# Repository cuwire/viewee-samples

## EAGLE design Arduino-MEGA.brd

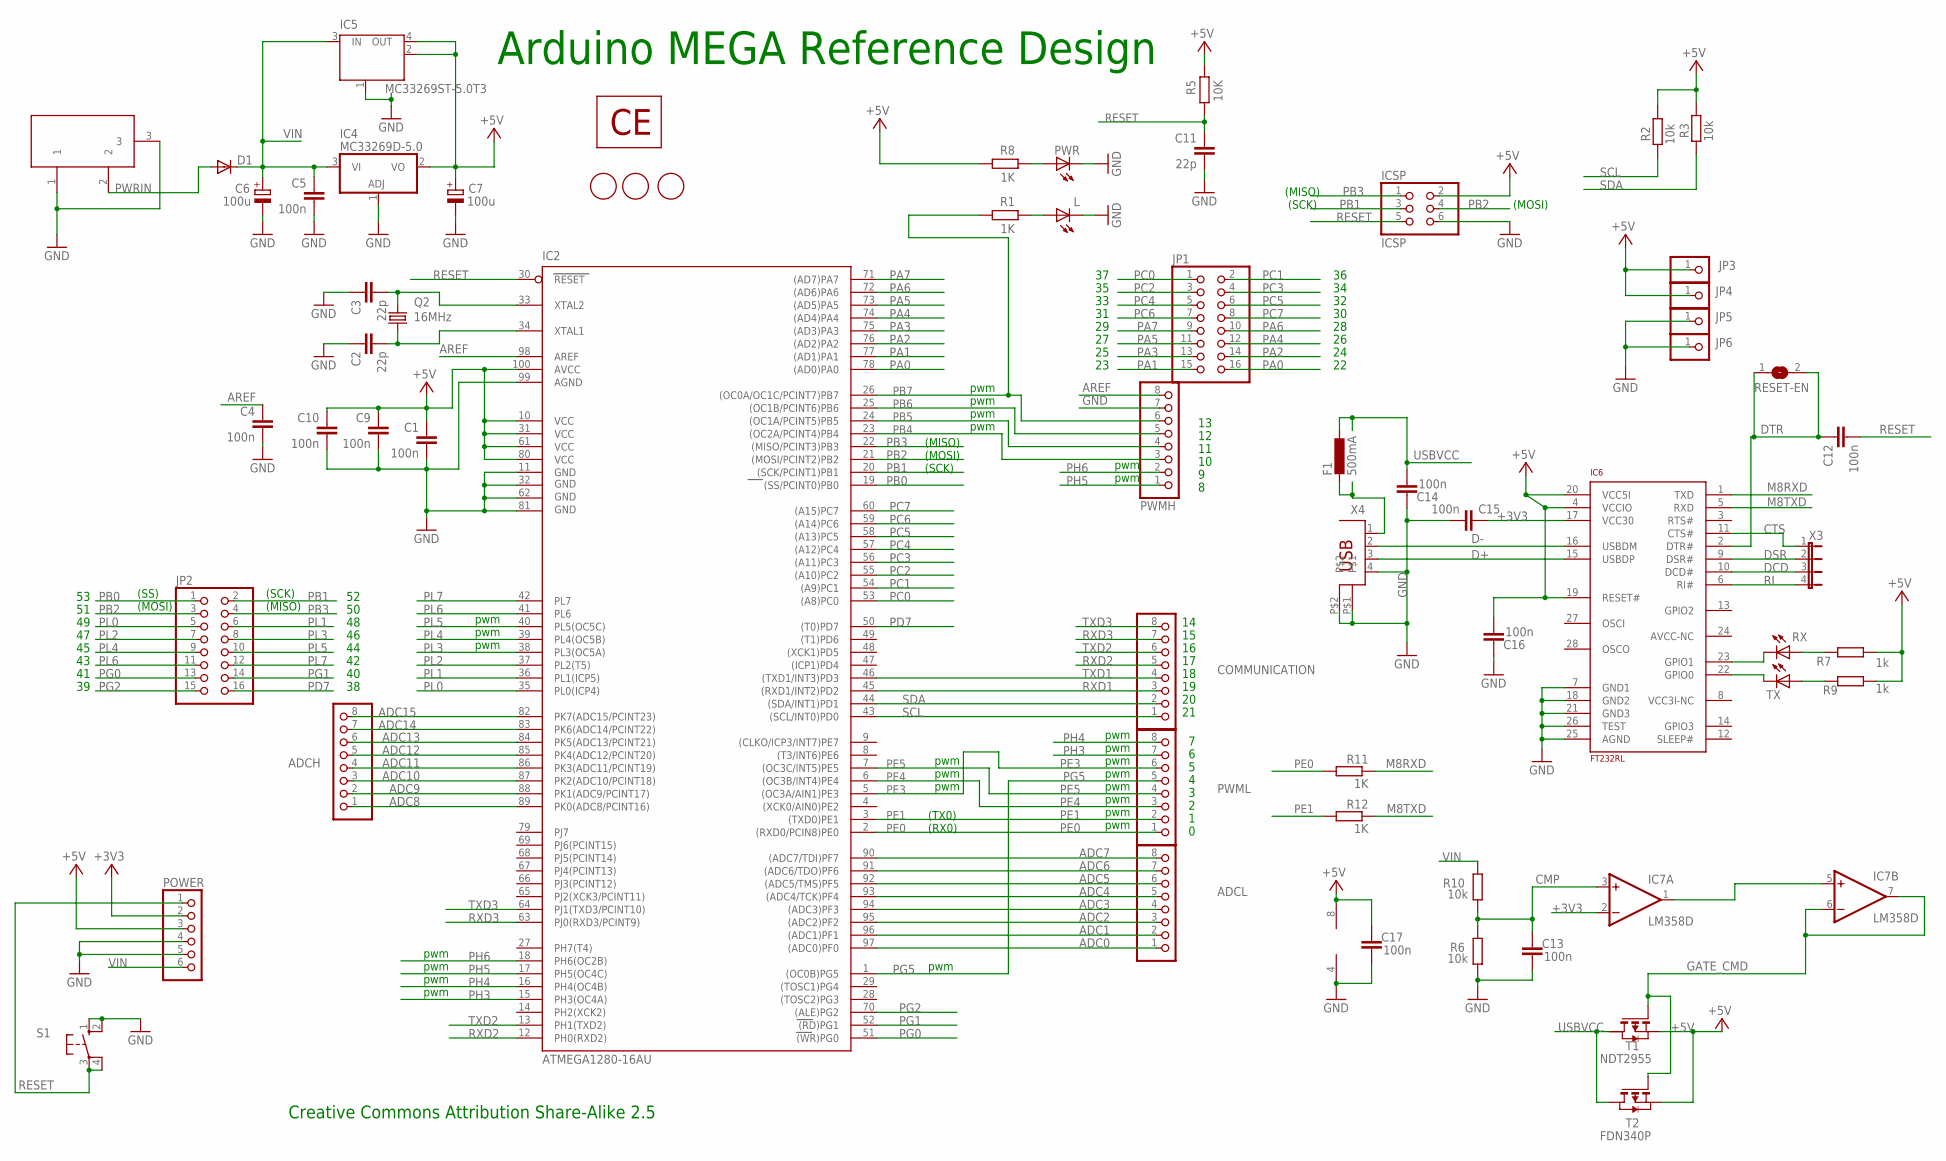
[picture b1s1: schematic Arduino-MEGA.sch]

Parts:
ADCH: PINHD-1X8; 1X08
ADCL: PINHD-1X8; 1X08
C1, C4, C5, C9, C10, C12, C13, C14, C15, C16, C17: 100n; C0805RND
C2, C3, C11: 22p; C0805RND
C6, C7: 100u; SMC_D
COMMUNICATION: PINHD-1X8; 1X08
D1: DIODE-SMB; SMB
F1: 500mA; L1812
IC2: ATMEGA1280-16AU; TQFP100
IC4: MC33269D-5.0; DPACK
IC5: MC33269ST-5.0T3; SOT223
IC6: FT232RL; SSOP28
IC7: LM358D; SO08
ICSP: ICSP; 2X03
JP1, JP2: PINHD-2X8; 2X08
JP3, JP4, JP5, JP6: PINHD-1X1; 1X01
L: LED0805ROUND; 0805RND
POWER: PINHD-1X6; 1X06
PWMH: PINHD-1X8; 1X08
PWML: PINHD-1X8; 1X08
PWR: LED0805ROUND; 0805RND
Q2: 16MHz; HC49/S
R1, R8: 1K; R0805RND
R2, R3, R6, R10: 10k; R0805RND
R5: 10K; R0805RND
R7, R9: 1k; R0805RND
R11, R12: 1K; RCL_0805RND
RESET-EN: SJ
RX: LED0805ROUND; 0805RND
S1: 10-XX; B3F-10XX
T1: NDT2955; SOT223
T2: FDN340P; SOT-23
TX: LED0805ROUND; 0805RND
U$1, U$2, U$3: FIDUCIALMOUNT; FIDUCIA-MOUNT
U$4: CE; CE-COPPER
X2: DC21MMX; DC-21MM
X3: JP4E; JP4
X4: PN61729

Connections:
+3V3: C15.2, IC6.17 (VCC30), IC7.2 (-IN), POWER.2
+5V: C1.1, C7.+, C9.1, C10.1, C16.1, C17.2, IC2.10 (VCC), IC2.31 (VCC1), IC2.61 (VCC2), IC2.80 (VCC3), IC2.100 (AVCC), IC4.2 (VO), IC5.2 (OUT), IC5.4 (OUT), IC6.4 (VCCIO), IC6.19 (RESET#), IC6.20 (VCC5I), IC7.8 (V+), ICSP.2, JP3.1, JP4.1, POWER.3, R2.1, R3.1, R5.2, R7.2, R8.1, R9.2, T1.3 (S), T2.2 (S)
ADC0: ADCL.1, IC2.97 ((ADC0)PF0)
ADC1: ADCL.2, IC2.96 ((ADC1)PF1)
ADC2: ADCL.3, IC2.95 ((ADC2)PF2)
ADC3: ADCL.4, IC2.94 ((ADC3)PF3)
ADC4: ADCL.5, IC2.93 ((ADC4/TCK)PF4)
ADC5: ADCL.6, IC2.92 ((ADC5/TMS)PF5)
ADC6: ADCL.7, IC2.91 ((ADC6/TDO)PF6)
ADC7: ADCL.8, IC2.90 ((ADC7/TDI)PF7)
ADC8: ADCH.1, IC2.89 (PK0(ADC8/PCINT16))
ADC9: ADCH.2, IC2.88 (PK1(ADC9/PCINT17))
ADC10: ADCH.3, IC2.87 (PK2(ADC10/PCINT18))
ADC11: ADCH.4, IC2.86 (PK3(ADC11/PCINT19))
ADC12: ADCH.5, IC2.85 (PK4(ADC12/PCINT20))
ADC13: ADCH.6, IC2.84 (PK5(ADC13/PCINT21))
ADC14: ADCH.7, IC2.83 (PK6(ADC14/PCINT22))
ADC15: ADCH.8, IC2.82 (PK7(ADC15/PCINT23))
AREF: C4.1, IC2.98 (AREF), PWMH.8
CMP: C13.2, IC7.3 (+IN), R6.2, R10.1
CTS: IC6.11 (CTS#), X3.1
D+: IC6.15 (USBDP), X4.3
D-: IC6.16 (USBDM), X4.2
DCD: IC6.10 (DCD#), X3.3
DSR: IC6.9 (DSR#), X3.2
DTR: C12.1, IC6.2 (DTR#), RESET-EN.1, RESET-EN.2
GATE_CMD: IC7.6 (-IN), IC7.7 (OUT), T1.1 (G), T2.3 (G)
GND: C1.2, C2.1, C3.1, C4.2, C5.2, C6.-, C7.-, C9.2, C10.2, C11.2, C13.1, C14.2, C15.1, C16.2, C17.1, IC2.11 (GND), IC2.32 (GND1), IC2.62 (GND2), IC2.81 (GND3), IC2.99 (AGND), IC4.1 (ADJ), IC5.1 (GND/ADJ), IC6.7 (GND1), IC6.18 (GND2), IC6.21 (GND3), IC6.25 (AGND), IC6.26 (TEST), IC7.4 (V-), ICSP.6, JP5.1, JP6.1, L.P$2 (C), POWER.4, POWER.5, PWMH.7, PWR.P$2 (C), R6.1, S1.1 (S), S1.2 (S1), X2.1, X2.3, X4.4, X4.P$1, X4.P$2
M8RXD: IC6.1 (TXD), R11.P$1 (1)
M8TXD: IC6.5 (RXD), R12.P$1 (1)
unnamed: L.P$1 (A), R1.2
unnamed: PWR.P$1 (A), R8.2
unnamed: IC7.1 (OUT), IC7.5 (+IN)
unnamed: C2.2, IC2.34 (XTAL1), Q2.1
unnamed: C3.2, IC2.33 (XTAL2), Q2.2
unnamed: IC6.23 (GPIO1), RX.P$2 (C)
unnamed: IC6.22 (GPIO0), TX.P$2 (C)
unnamed: R7.1, RX.P$1 (A)
unnamed: R9.1, TX.P$1 (A)
unnamed: F1.2, X4.1
PA0: IC2.78 ((AD0)PA0), JP1.16
PA1: IC2.77 ((AD1)PA1), JP1.15
PA2: IC2.76 ((AD2)PA2), JP1.14
PA3: IC2.75 ((AD3)PA3), JP1.13
PA4: IC2.74 ((AD4)PA4), JP1.12
PA5: IC2.73 ((AD5)PA5), JP1.11
PA6: IC2.72 ((AD6)PA6), JP1.10
PA7: IC2.71 ((AD7)PA7), JP1.9
PB0: IC2.19 ((SS/PCINT0)PB0), JP2.1
PB1: IC2.20 ((SCK/PCINT1)PB1), ICSP.3, JP2.2
PB2: IC2.21 ((MOSI/PCINT2)PB2), ICSP.4, JP2.3
PB3: IC2.22 ((MISO/PCINT3)PB3), ICSP.1, JP2.4
PB4: IC2.23 ((OC2A/PCINT4)PB4), PWMH.3
PB5: IC2.24 ((OC1A/PCINT5)PB5), PWMH.4
PB6: IC2.25 ((OC1B/PCINT6)PB6), PWMH.5
PB7: IC2.26 ((OC0A/OC1C/PCINT7)PB7), PWMH.6, R1.1
PC0: IC2.53 ((A8)PC0), JP1.1
PC1: IC2.54 ((A9)PC1), JP1.2
PC2: IC2.55 ((A10)PC2), JP1.3
PC3: IC2.56 ((A11)PC3), JP1.4
PC4: IC2.57 ((A12)PC4), JP1.5
PC5: IC2.58 ((A13)PC5), JP1.6
PC6: IC2.59 ((A14)PC6), JP1.7
PC7: IC2.60 ((A15)PC7), JP1.8
PD7: IC2.50 ((T0)PD7), JP2.16
PE0: IC2.2 ((RXD0/PCIN8)PE0), PWML.1, R11.P$2 (2)
PE1: IC2.3 ((TXD0)PE1), PWML.2, R12.P$2 (2)
PE3: IC2.5 ((OC3A/AIN1)PE3), PWML.6
PE4: IC2.6 ((OC3B/INT4)PE4), PWML.3
PE5: IC2.7 ((OC3C/INT5)PE5), PWML.4
PG0: IC2.51 ((WR)PG0), JP2.13
PG1: IC2.52 ((RD)PG1), JP2.14
PG2: IC2.70 ((ALE)PG2), JP2.15
PG5: IC2.1 ((OC0B)PG5), PWML.5
PH3: IC2.15 (PH3(OC4A)), PWML.7
PH4: IC2.16 (PH4(OC4B)), PWML.8
PH5: IC2.17 (PH5(OC4C)), PWMH.1
PH6: IC2.18 (PH6(OC2B)), PWMH.2
PL0: IC2.35 (PL0(ICP4)), JP2.5
PL1: IC2.36 (PL1(ICP5)), JP2.6
PL2: IC2.37 (PL2(T5)), JP2.7
PL3: IC2.38 (PL3(OC5A)), JP2.8
PL4: IC2.39 (PL4(OC5B)), JP2.9
PL5: IC2.40 (PL5(OC5C)), JP2.10
PL6: IC2.41 (PL6), JP2.11
PL7: IC2.42 (PL7), JP2.12
PWRIN: D1.A, X2.2
RESET: C11.1, C12.2, IC2.30 (RESET), ICSP.5, POWER.1, R5.1, S1.3, S1.4 (P1)
RI: IC6.6 (RI#), X3.4
RXD1: COMMUNICATION.3, IC2.45 ((RXD1/INT2)PD2)
RXD2: COMMUNICATION.5, IC2.12 (PH0(RXD2))
RXD3: COMMUNICATION.7, IC2.63 (PJ0(RXD3/PCINT9))
SCL: COMMUNICATION.1, IC2.43 ((SCL/INT0)PD0), R2.2
SDA: COMMUNICATION.2, IC2.44 ((SDA/INT1)PD1), R3.2
TXD1: COMMUNICATION.4, IC2.46 ((TXD1/INT3)PD3)
TXD2: COMMUNICATION.6, IC2.13 (PH1(TXD2))
TXD3: COMMUNICATION.8, IC2.64 (PJ1(TXD3/PCINT10))
USBVCC: C14.1, F1.1, T1.2 (D), T2.1 (D)
VIN: C5.1, C6.+, D1.C, IC4.3 (VI), IC5.3 (IN), POWER.6, R10.2

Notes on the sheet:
Arduino MEGA Reference Design
(SCK)
(MISO)
(MOSI)
pwm
(TX0)
(RX0)
(SS)
Creative Commons Attribution Share-Alike 2.5

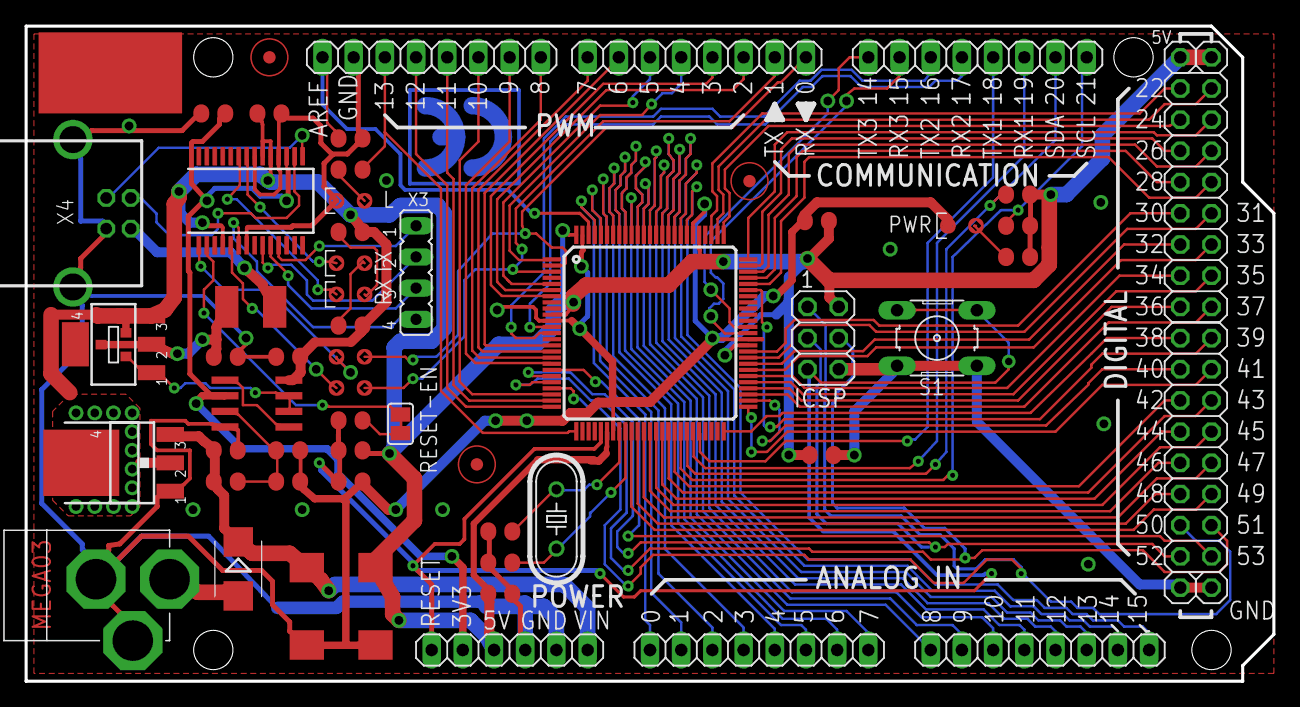
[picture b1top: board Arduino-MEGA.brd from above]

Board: 2 copper layers, 101.6 x 53.3 mm, 63 parts (1 on the bottom side), 99 nets.

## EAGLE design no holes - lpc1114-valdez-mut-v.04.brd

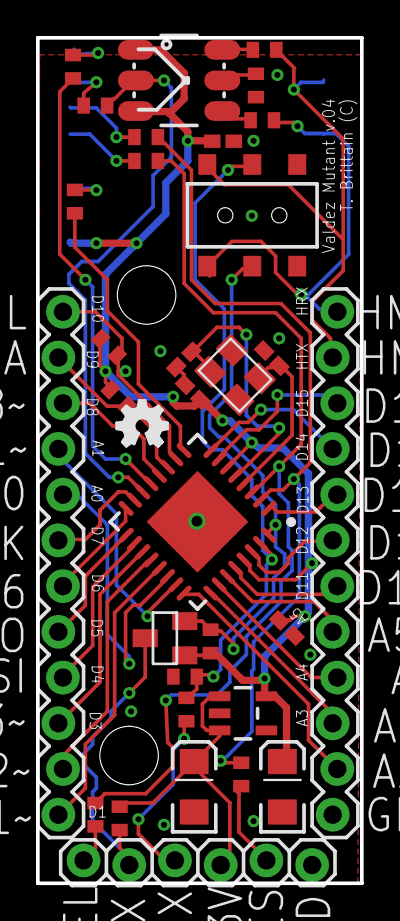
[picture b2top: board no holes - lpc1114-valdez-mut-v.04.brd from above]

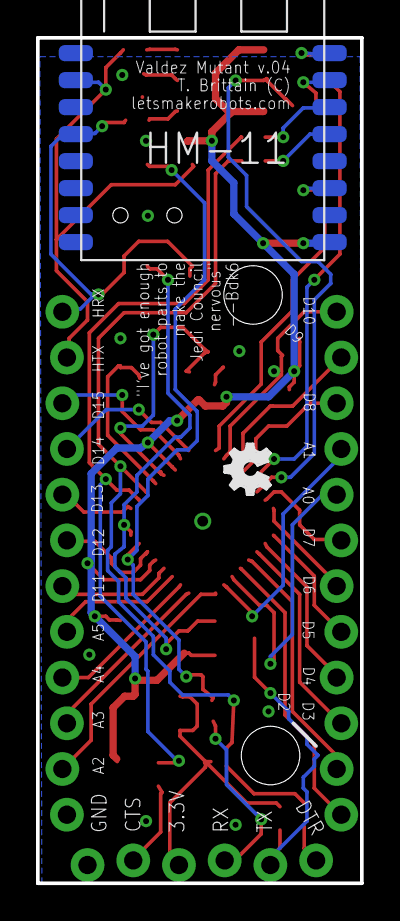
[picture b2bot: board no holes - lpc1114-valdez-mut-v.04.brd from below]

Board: 2 copper layers, 18.0 x 47.0 mm, 35 parts (2 on the bottom side), 47 nets.

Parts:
12.5MHZ: CRYSTAL_SMD_3.2X2.5
AP2112K-3.3TRG1: V_REG_LDOSMD; SOT23-5
C1, C4: 10uF; EIA3216
C2, C3: 22pF; C0402K
C5, C6, C7: 1uF; C0402K
JP1, JP2: M12LOCK; 1X12_LOCK
JP3: 1X06_LOCK
JS202011SCQN: DPDT; AYZ0202
LED1: LED-TRICOLOR-5050NO_IC; LED-TRICOLOR-5050
Q2: BSS138; SOT23
R1, R12, R13, R14, R15, R16: 330; R0402
R2: 1k; R0402
R3, R4, R6: 10k; R0402
R5: 20k; R0402
R7, R8, R9: 470; R0402
R10, R11: 4.7K; R0402
U1: HVQFN33-7X7
U$1: HM-11
U$2, U$3: OSHW_FILLX100_NOTEXT

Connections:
3.3V: AP2112K-3.3TRG1.5, C4.A, C5.1, C6.1, C7.1, LED1.1, LED1.3, Q2.1, R4.2, R10.1, R11.1, U1.P$6, U1.P$29, U$1.9
5V: AP2112K-3.3TRG1.1, AP2112K-3.3TRG1.3, C1.A, JP3.4, R3.2
BUTTON?: R15.2, U$1.16
CONN: R14.2, U$1.15
GND: AP2112K-3.3TRG1.2, C1.C, C2.1, C3.1, C4.C, C5.2, C6.2, C7.2, JP2.1, JP3.6, R5.2, R7.1, U1.P$33, U$1.12
HM-RX: JP2.12, JS202011SCQN.4, R9.1, U$1.4
HM-TX: JP2.11, JS202011SCQN.1, R8.1, U$1.2
HM_BUTTON?: R15.1, U1.P$13
HM_CONN: LED1.2, R14.1, U1.P$14
IO20: JP2.8, U1.P$1
IO_00_RES: R1.2, R12.1, U1.P$2
IO_02: JP2.9, U1.P$8
IO_03: R2.2, U1.P$9
IO_05-SDA: JP1.11, R11.2, U1.P$11
IO_06: JP1.7, U1.P$15
IO_07: JP1.6, U1.P$16
IO_08: JP1.5, U1.P$17
IO_08-SCL: JP1.12, R10.2, U1.P$10
IO_09: JP1.4, U1.P$18
IO_10: JP1.8, U1.P$22
IO_010: JP1.3, U1.P$19
IO_11: JP1.9, U1.P$23
IO_011: JP1.1, U1.P$21
IO_12: JP2.2, U1.P$24
IO_13: JP2.3, U1.P$25
IO_14: JP2.4, U1.P$26
IO_15: JP2.7, U1.P$30
IO_18: JP2.10, U1.P$7
IO_19: JP1.10, U1.P$12
IO_32: JP2.6, U1.P$28
IO_110: JP1.2, U1.P$20
IO_111: JP2.5, U1.P$27
LPC_RES: R12.2, U$1.14
LPC_SEL: R13.1, R16.2, U1.P$3
LPC_SEL_BOOT: R13.2, U$1.13
unnamed: LED1.4, R9.2
unnamed: LED1.6, R8.2
unnamed: LED1.5, R7.2
unnamed: R2.1, U$1.11
unnamed: 12.5MHZ.3, C3.2, U1.P$4
unnamed: 12.5MHZ.1, C2.2, U1.P$5
RESET: JP3.5, R1.1
RX: JS202011SCQN.2, R5.1, R6.2, U1.P$31
RX-5V: JP3.3, R6.1
SEL: JP3.1, R16.1
TX: JS202011SCQN.5, Q2.2, R4.1, U1.P$32
TX-5V: JP3.2, Q2.3, R3.1

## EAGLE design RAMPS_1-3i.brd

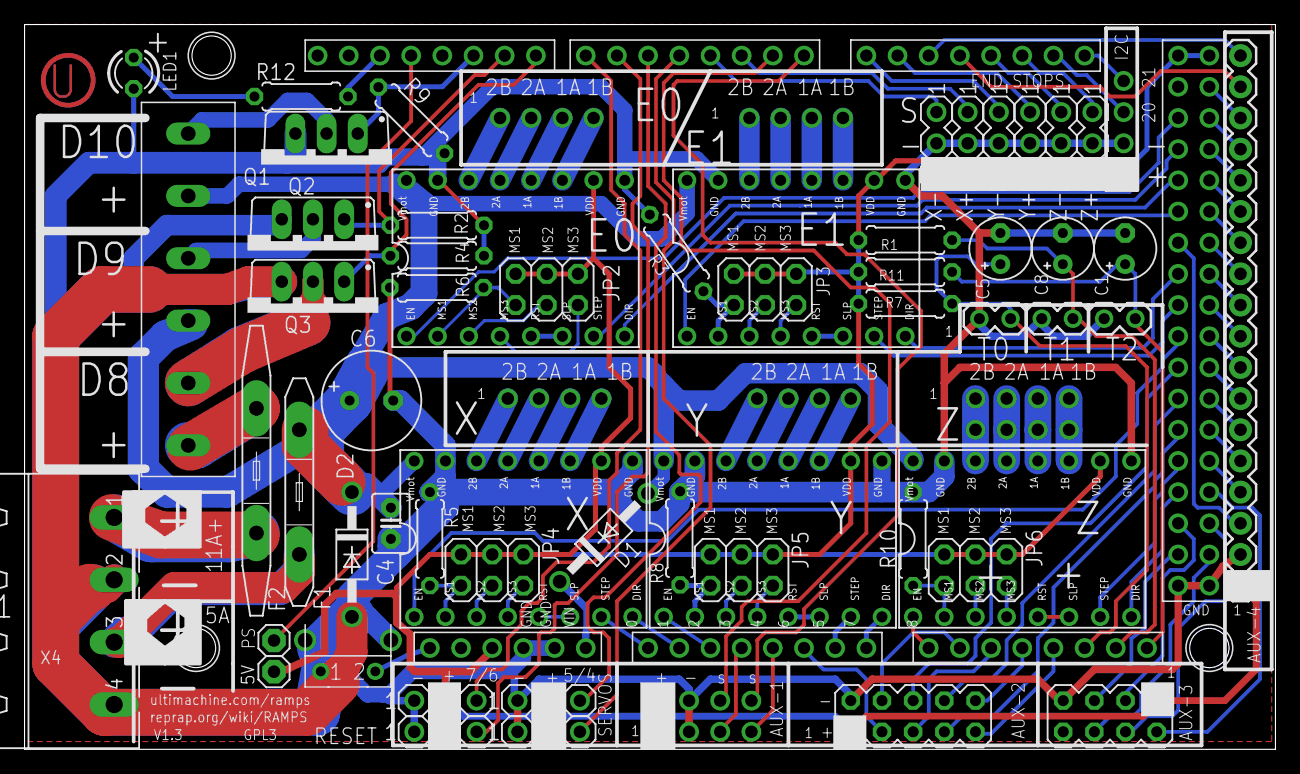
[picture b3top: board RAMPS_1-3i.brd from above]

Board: 2 copper layers, 101.9 x 59.0 mm, 64 parts (0 on the bottom side), 120 nets.

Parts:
5V: 1X01
A-OUT: 1X04
C1, C5, C8: 10uF; E2,5-5
C4: 100nF; C2.5-3
C6: 470uF; E3,5-8
D1, D2: 1N4004; DO41-10
E0-MOT, E1-MOT: 1X04
F1: MFR500
F2: MFR1100
I2C: 1X04
JP2, JP3, JP4, JP5, JP6: 2X03
JP7: 1X06
LED1: LED3MM
PS-ON: 1X01
Q1, Q2, Q3: STP55NF06L; TO220BV
R1, R7, R11: 4.7K; 0207/7
R2, R3, R4, R5, R6, R8, R9, R10: 100k; 0207/7
R12: 1K; 0207/7
SER1, SER2, SER3, SER4: 3PIN-HEADER
SERIAL: 1X04
U1: ARDUINO_MEGA_SHIELD
U$1: FSMRACD
U$2: 282837-6
U$3: M04X2; 2X4
U$4, U$5, U$6, U$7, U$8: A4988BREAKOUT
U$9: M18_; 1X18
U$10: M05X2; 2X5
X4: MSTBA4
X+: 3PIN-HEADER
X-: 3PIN-HEADER
X-MOT: 1X04
Y+: 3PIN-HEADER
Y-: 3PIN-HEADER
Y-MOT: 1X04
Z+: 3PIN-HEADER
Z-: 3PIN-HEADER
Z-MOT, Z-MOT1: 1X04

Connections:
+12V: C4.1, C6.+, D1.A, D2.C, F1.1, U$2.P$3, U$2.P$5, U$4.VMOT, U$5.VMOT, U$6.VMOT, U$7.VMOT, U$8.VMOT
+12V2: F2.2, U$2.P$1
A3: SERIAL.3, U1.A3
A4: SERIAL.4, U1.A4
A5: U1.A5, U$10.3
A9: U1.A9, U$10.4
A10: U1.A10, U$10.5
A11: U1.A11, U$10.10
A12: U1.A12, U$10.9
AM-VIN: D1.C, U1.VIN
D1: A-OUT.4, U1.RX
D2: A-OUT.3, U1.TX
D4: SER4.3, U1.D4
D5: SER3.3, U1.D5
D6: SER2.3, U1.D6
D7: SER1.3, U1.D7
D8: Q3.G, R4.1, U1.D8
D9: Q2.G, R2.1, U1.D9
D10: Q1.G, R9.1, U1.D10
D12: PS-ON.1, U1.D12
D16: U1.D16, U$9.18
D17: U1.D17, U$9.17
D23: U1.D23, U$9.16
D25: U1.D25, U$9.15
D27: U1.D27, U$9.14
D29: U1.D29, U$9.13
D31: U1.D31, U$9.12
D32: U1.D32, U$9.3
D33: U1.D33, U$9.11
D35: U1.D35, U$9.10
D37: U1.D37, U$9.9
D39: U1.D39, U$9.8
D40: U1.D40, U$10.6
D41: U1.D41, U$9.7
D42: U1.D42, U$10.8
D43: U1.D43, U$9.6
D44: U1.D44, U$10.7
D45: U1.D45, U$9.5
D47: U1.D47, U$9.4
D49: U1.D49, U$3.2
D53: U1.D53, U$3.6
E0-DIR: U1.D28, U$4.DIR
E0-EN: U1.D24, U$4.EN
E0-STEP: U1.D26, U$4.STEP
E1-DIR: U1.D34, U$5.DIR
E1-EN: U1.D30, U$5.EN
E1-STEP: U1.D36, U$5.STEP
GND: A-OUT.2, C1.-, C4.2, C5.-, C6.-, C8.-, D2.A, I2C.2, JP7.1, JP7.3, JP7.5, LED1.K, Q1.S, Q2.S, Q3.S, R2.2, R3.2, R4.2, R5.2, R6.1, R8.2, R9.2, R10.2, SER1.1, SER2.1, SER3.1, SER4.1, SERIAL.2, U1.GND@0, U1.GND@1, U1.GND@3, U1.GND@4, U$1.GND1, U$1.GND2, U$1.P$1, U$3.7, U$4.GND, U$4.GND@0, U$5.GND, U$5.GND@0, U$6.GND, U$6.GND@0, U$7.GND, U$7.GND@0, U$8.GND, U$8.GND@0, U$9.2, U$10.2, X4.2, X4.4, X+.2, X-.2, Y+.2, Y-.2, Z+.2, Z-.2
LED: R12.2, U1.D13
MISO: U1.D50, U$3.3
MOSI: U1.D51, U$3.4
unnamed: Q2.D, U$2.P$4
unnamed: Q3.D, U$2.P$2
unnamed: E0-MOT.1, U$4.2B
unnamed: E0-MOT.2, U$4.2A
unnamed: JP2.1, R6.2, U$4.MS1
unnamed: JP2.5, U$4.MS3
unnamed: Q1.D, U$2.P$6
unnamed: U$4.RST, U$4.SLP
unnamed: JP2.3, U$4.MS2
unnamed: E0-MOT.3, U$4.1A
unnamed: E0-MOT.4, U$4.1B
unnamed: E1-MOT.1, U$5.2B
unnamed: E1-MOT.2, U$5.2A
unnamed: JP4.1, R5.1, U$6.MS1
unnamed: JP4.3, U$6.MS2
unnamed: E1-MOT.3, U$5.1A
unnamed: JP5.3, U$7.MS2
unnamed: E1-MOT.4, U$5.1B
unnamed: JP4.5, U$6.MS3
unnamed: U$6.RST, U$6.SLP
unnamed: U$6.2B, X-MOT.1
unnamed: U$6.2A, X-MOT.2
unnamed: U$7.RST, U$7.SLP
unnamed: U$5.RST, U$5.SLP
unnamed: JP3.1, R3.1, U$5.MS1
unnamed: U$6.1A, X-MOT.3
unnamed: U$6.1B, X-MOT.4
unnamed: U$7.2B, Y-MOT.1
unnamed: U$7.2A, Y-MOT.2
unnamed: U$7.1A, Y-MOT.3
unnamed: JP5.5, U$7.MS3
unnamed: F1.2, X4.3
unnamed: JP5.1, R8.1, U$7.MS1
unnamed: JP3.5, U$5.MS3
unnamed: JP3.3, U$5.MS2
unnamed: U$7.1B, Y-MOT.4
unnamed: JP6.3, U$8.MS2
unnamed: U$8.RST, U$8.SLP
unnamed: JP6.5, U$8.MS3
unnamed: JP6.1, R10.1, U$8.MS1
unnamed: U$8.2B, Z-MOT.1, Z-MOT1.1
unnamed: U$8.2A, Z-MOT.2, Z-MOT1.2
unnamed: U$8.1A, Z-MOT.3, Z-MOT1.3
unnamed: U$8.1B, Z-MOT.4, Z-MOT1.4
unnamed: F2.1, X4.1
unnamed: LED1.A, R12.1
RESET: U1.RES, U$1.P$2
SCK: U1.D52, U$3.5
SCL: I2C.4, U1.D21
SDA: I2C.3, U1.D20
THERM0: C5.+, JP7.2, R7.1, U1.A13
THERM1: C8.+, JP7.4, R1.1, U1.A14
THERM2: C1.+, JP7.6, R11.1, U1.A15
VCC: 5V.1, A-OUT.1, I2C.1, JP2.2, JP2.4, JP2.6, JP3.2, JP3.4, JP3.6, JP4.2, JP4.4, JP4.6, JP5.2, JP5.4, JP5.6, JP6.2, JP6.4, JP6.6, R1.2, R7.2, R11.2, SER1.2, SER2.2, SER3.2, SER4.2, SERIAL.1, U1.5V@0, U1.5V@1, U1.5V@2, U$3.1, U$4.VDD, U$5.VDD, U$6.VDD, U$7.VDD, U$8.VDD, U$9.1, U$10.1, X+.3, X-.3, Y+.3, Y-.3, Z+.3, Z-.3
X-DIR: U1.A1, U$6.DIR
X-EN: U1.D38, U$6.EN
X-MAX: U1.D2, X+.1
X-MIN: U1.D3, X-.1
X-STEP: U1.A0, U$6.STEP
Y-DIR: U1.A7, U$7.DIR
Y-EN: U1.A2, U$7.EN
Y-MAX: U1.D15, Y+.1
Y-MIN: U1.D14, Y-.1
Y-STEP: U1.A6, U$7.STEP
Z-DIR: U1.D48, U$8.DIR
Z-EN: U1.A8, U$8.EN
Z-MAX: U1.D19, Z+.1
Z-MIN: U1.D18, Z-.1
Z-STEP: U1.D46, U$8.STEP

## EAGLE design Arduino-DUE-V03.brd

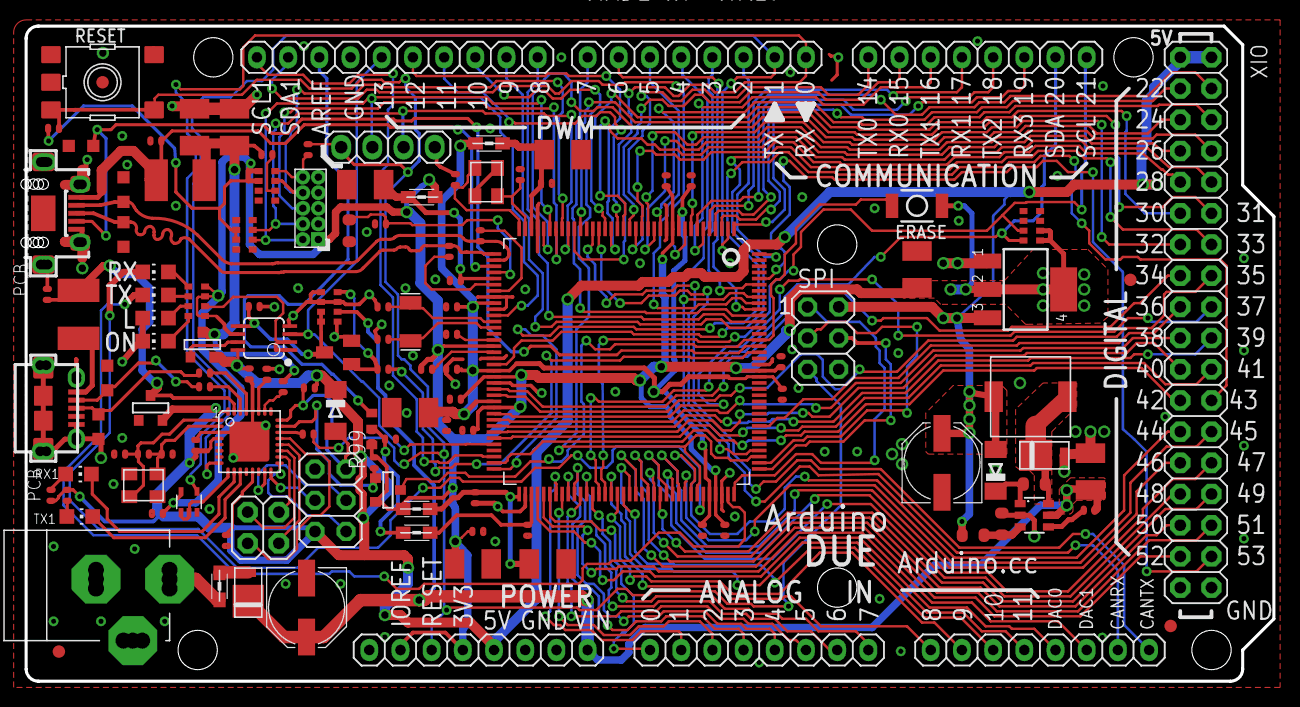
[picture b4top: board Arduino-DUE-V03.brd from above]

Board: 2 copper layers, 101.6 x 53.3 mm, 129 parts (0 on the bottom side), 150 nets.

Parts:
ADCH: 8x1F-H8.5; 1X08
ADCL: 8x1F-H8.5; 1X08
BR1: NM; J0402
C1, C2, C3, C11, C27, C29, C33, C35, C41: 10u; SMC_B
C4, C5, C6, C7, C8, C9, C10, C12, C13, C14, C15, C16, C17, C18, C19, C28, C30, C31, C32, C34, C36, C37: 100n; C0402
C20, C26: 10n; C0402
C21, C22, C25, C39, C40: 22p; C0402
C23, C24: 22pF_NM; C0402
C38: 1u; C0402
C42: 10n; C0603-ROUND
COMMUNICATION: 8x1F-H8.5; 1X08
D2, D3: CD1206-S01575; MINIMELF
D4, D5: SS1P3L; DO220AAL
DEBUG: STRIP 4x1V M; 1X04
ERASE: SMD_157SW
F1, F2: MF-MSMF050-2 500mA; L1812
FID1, FID2, FID3, FID4: FIDUCIALMOUNT; FIDUCIA-MOUNT
IC1: LMV358IDGKR; MSOP08
IC2: LM2734Y; SOT23-6
IC4: NCP1117ST33T3G -3V3; SOT223
IC6: ATMEGA16U2-MU; MLF32
IC10: 74LVC1G125DCK; SC70-5
ICSP1: 3x2M; 2X03
J3: USB-MICRO B; CON2_USB_MICRO_B_AT
JP5: 2x2M - NM; 2X02
JR1: 0R; R0402
JTAG: PINHEAD_2X05_127
L: YELLOW; CHIP-LED0805
L1, L2, L3, L5, L6: MH2029-300Y; 0805
L4: 10u SRR0604-100ML; SRR0604
ON: GREEN; CHIP-LED0805
PC1, PC2: 47u; PANASONIC_D
POWER: 8x1F-H8.5; 1X08
PWMH: 10x1F-H8.5; 1X10
PWML: 8x1F-H8.5; 1X08
Q2: BC847BSMD; SOT23
R1: 0R; R0402
R2, R13, R18, R99: 10K; R0402
R3, R14, R15, R21, R23: 1K; R0402
R4: 100K; R0402
R5, R6: 39R 1%; R0402
R7: 6k8 1%; R0603-ROUND
R8: 0R_NM; R0402
R9: 1M_NM; R0402
R10: 10k; R0402
R11: 10K; R0603-ROUND
R12: 52K3; R0603-ROUND
R19, R20: 22R; R0402
RESET: TS42
RN1, RN2, RN4: 100K; CAT16
RN3: 1k; CAY16
RN5: 1K5; CAT16
RX, RX1: YELLOW; CHIP-LED0805
SPI: 3x2M; 2X03
T1, T2, T3: FDN340P; SOT-23
TX, TX1: YELLOW; CHIP-LED0805
U1: ATSAM3X8EA-AU; LQFP144
USB1: MICRO-USB-AB1; MCR-AB1-S-RA-SMT
X2: POWERSUPPLY_DC21MMX; POWERSUPPLY_DC-21MM
XIO: 18x2F-H8.5; 2X18
Y1: 12MHz KX-7 20pF; CRYSTAL-3.2-2.5
Y2: 32.768Khz; RESONATOR_EPSON_FC_145
Y4: 16MHz KX-7 20pF; CRYSTAL-3.2-2.5
Z1, Z2, Z3, Z4, Z5: CG0603MLC-05E; CT/CN0603

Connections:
8PB4: IC6.18, JP5.1
8PB5: IC6.19, JP5.3
8PB6: IC6.20, JP5.2
8PB7: IC6.21, JP5.4
16U2-TX: IC6.9, IC10.1, IC10.2
+3V3: BR1.3, C1.+, C4.2, C5.2, C6.2, C7.2, C8.2, C18.2, C20.2, C29.+, C37.1, ERASE.1, IC1.6, IC4.2, IC4.4, IC10.5, JR1.1, JTAG.1, L1.1, L2.1, POWER.2, POWER.4, R4.2, R99.2, RN1.5, RN1.6, RN2.2, RN2.3, RN3.5, RN3.7, RN3.8, RN5.1, RN5.2, T3.2, U1.11, U1.52, U1.57, U1.62, U1.105, U1.125
+5V: C30.2, C36.1, D2.C, D3.A, IC1.8, IC4.3, IC6.4, IC6.32, ICSP1.2, L4.P$2, PC2.+, POWER.5, R12.1, R13.2, R14.1, R15.1, SPI.2, T1.2, T2.2, XIO.1, XIO.2
AD0: ADCL.1, U1.78
AD1: ADCL.2, U1.79
AD2: ADCL.3, U1.80
AD3: ADCL.4, U1.81
AD4: ADCL.5, U1.82
AD5: ADCL.6, U1.83
AD6: ADCL.7, U1.84
AD7: ADCL.8, U1.85
AD8: ADCH.1, U1.88
AD9: ADCH.2, U1.89
AD10: ADCH.3, U1.90
AD11(TXD3): ADCH.4, U1.91
AD14(RXD3): U1.92, XIO.33
AREF: BR1.1, PWMH.8
AVREF: C19.2, L3.2, U1.75
AVREFL: BR1.2, C34.2, JR1.2, L3.1
BD+: J3.P3, R20.2, Z4.2
BD-: J3.P2, R19.2, Z3.2
BOOST: C42.1, D3.C, IC2.1
CANRX0: ADCH.7, U1.24
CANTX0: ADCH.8, U1.23
CANTX1/IO: U1.140, XIO.34
CMP: C31.2, IC1.5, Q2.3, RN4.3, RN4.4
D+: R6.1, U1.37, USB1.3, Z1.1
D-: R5.1, U1.38, USB1.2, Z2.1
DAC0(CANRX1): ADCH.5, U1.76
DAC1: ADCH.6, U1.77
DTR: IC6.13, R18.1
EN: IC2.4, R10.2
ERASE_CMD: IC6.23, R99.1, T3.3
ERASE_S: ERASE.2, T3.1, U1.130
FB: IC2.3, R11.1, R12.2
GATE_CMD: IC1.7, T1.3
GND: C1.-, C2.-, C3.-, C4.1, C5.1, C6.1, C7.1, C8.1, C9.1, C10.1, C11.-, C12.1, C13.1, C14.1, C15.1, C16.1, C17.1, C18.1, C19.1, C21.2, C22.2, C23.2, C24.2, C25.2, C26.2, C27.-, C28.2, C29.-, C30.1, C31.1, C32.1, C33.-, C34.1, C35.-, C36.2, C37.2, C38.2, C39.2, C40.2, C41.-, D4.P$2, DEBUG.1, IC1.4, IC2.2, IC4.1, IC6.3, IC6.28, IC6.33, IC10.3, ICSP1.6, J3.P5, J3.P$1, J3.P$2, J3.P$3, J3.P$4, J3.P$5, J3.P$6, J3.P$7, J3.P$8, J3.S1, J3.S2, J3.S3, J3.S4, J3.S5, J3.S6, JTAG.3, JTAG.5, JTAG.9, L.C, ON.C, PC1.-, PC2.-, POWER.6, POWER.7, PWMH.7, Q2.2, R2.1, R7.1, R8.1, R11.2, R18.2, RESET.1, RESET.2, RN1.1, RN1.2, RN1.7, RN1.8, RN2.1, RN2.4, RN2.5, RN2.8, RN4.1, RN4.2, RN4.5, RN4.7, SPI.6, T2.3, U1.12, U1.33, U1.44, U1.46, U1.54, U1.58, U1.74, U1.106, U1.126, USB1.5, USB1.P$1, USB1.P$2, USB1.P$3, USB1.P$4, USB1.P$5, USB1.P$6, USB1.P$7, USB1.P$8, USB1.P$9, USB1.P$10, USB1.P$11, USB1.S1, USB1.S2, USB1.S3, USB1.S4, X2.1, X2.3, XIO.35, XIO.36, Y1.2, Y1.4, Y4.2, Y4.4, Z1.2, Z2.2, Z3.1, Z4.1, Z5.1
JTAG_RESET: JTAG.10, R1.1, RN1.4
JTAG_TCK: DEBUG.2, JTAG.4, RN2.7, U1.28
JTAG_TDI: JTAG.8, RN1.3, U1.29
JTAG_TDO: JTAG.6, U1.30
JTAG_TMS: DEBUG.3, JTAG.2, RN2.6, U1.31
L13: IC1.1, IC1.2, RN3.6
MASTER-RESET: C20.1, DEBUG.4, POWER.3, R1.2, R23.2, RESET.3, RESET.4, SPI.5, U1.47
MISO: SPI.1, U1.108
MISO2: IC6.17, ICSP1.1
MOSI: SPI.4, U1.109
MOSI2: IC6.16, ICSP1.4
unnamed: IC6.26, R21.1
unnamed: L.A, RN3.3
unnamed: ON.A, RN3.4
unnamed: R15.2, RX1.A
unnamed: R8.2, U1.51
unnamed: Q2.1, R3.2, RN4.8
unnamed: R4.1, U1.53
unnamed: D5.P$2, L6.1
unnamed: R5.2, U1.43
unnamed: R6.2, U1.42
unnamed: R14.2, TX1.A
unnamed: RN3.1, RX.A
unnamed: RN3.2, TX.A
PIN22: U1.1, XIO.3
PIN23: U1.7, XIO.4
PIN24: U1.8, XIO.5
PIN25: U1.13, XIO.6
PIN26: U1.14, XIO.7
PIN27: U1.15, XIO.8
PIN28: U1.16, XIO.9
PIN29: U1.19, XIO.10
PIN30: U1.22, XIO.11
PIN31: U1.26, XIO.12
PIN32: U1.32, XIO.13
PIN33: U1.55, XIO.14
PIN34: U1.59, XIO.15
PIN35: U1.60, XIO.16
PIN36: U1.116, XIO.17
PIN37: U1.63, XIO.18
PIN38: U1.64, XIO.19
PIN39: U1.65, XIO.20
PIN40: U1.66, XIO.21
PIN41: U1.67, XIO.22
PIN42: U1.71, XIO.23
PIN43: U1.72, XIO.24
PIN44: U1.101, XIO.25
PIN45: U1.100, XIO.26
PIN46: U1.99, XIO.27
PIN47: U1.98, XIO.28
PIN48: U1.97, XIO.29
PIN49: U1.96, XIO.30
PIN50: U1.95, XIO.31
PIN51: U1.94, XIO.32
PWM2: PWML.3, U1.144
PWM3: PWML.4, U1.139
PWM5: PWML.6, U1.136
PWM6: PWML.7, U1.135
PWM7: PWML.8, U1.134
PWM8: PWMH.1, U1.133
PWM9: PWMH.2, U1.132
PWM11: PWMH.4, U1.20
PWM12: PWMH.5, U1.21
PWM13: IC1.3, PWMH.6, U1.68
RD+: IC6.29, R20.1
RD-: IC6.30, R19.1
RESET2: D2.A, IC6.24, ICSP1.5, R13.1
RESET_CMD: IC6.22, R23.1
RX: IC10.4, PWML.1, U1.27
RXD0: COMMUNICATION.2, U1.18
RXD1: COMMUNICATION.4, U1.5
RXD2: COMMUNICATION.6, U1.3
RXL: RX.C, U1.103
RXL-U2: IC6.10, RX1.C
SCK2: IC6.15, ICSP1.3
SCL0-3: COMMUNICATION.8, RN5.7, U1.87
SCL1: PWMH.10, U1.70
SDA0-3: COMMUNICATION.7, RN5.8, U1.86
SDA1: PWMH.9, U1.9
SPCK: SPI.3, U1.110
SS0/PWM10: PWMH.3, U1.102, U1.111
SS1/PWM4: PWML.5, U1.112, U1.137
SW: C42.2, D4.P$1, IC2.6, L4.P$1
TX: IC6.8, PWML.2, U1.2
TXD0: COMMUNICATION.1, U1.17
TXD1: COMMUNICATION.3, U1.6
TXD2: COMMUNICATION.5, U1.4
TXL: TX.C, U1.107
TXL-U2: IC6.11, TX1.C
UOTGID: U1.129, USB1.4, Z5.2
UOTGVBOF: R3.1, U1.128
USBVCC: C27.+, C35.+, F1.1, R2.2, R21.2, T1.1
USBVCCU2: C28.1, F2.1, IC6.31, T2.1
VBG: C25.1, R7.2, U1.40
VDDANA: C3.+, C10.2, L1.2, U1.73
VDDOUT: C11.+, C12.2, C13.2, C14.2, C15.2, C16.2, C17.2, L5.1, U1.10, U1.45, U1.56, U1.61, U1.104, U1.124
VDDOUTMI: C2.+, C9.2, L2.2, U1.41
VDDPLL: C32.2, C33.+, L5.2, U1.34
VIN: C41.+, D5.P$1, IC2.5, PC1.+, POWER.8, R10.1, RN4.6
VIN+: L6.2, X2.2
VUCAP: C38.1, IC6.27
XIN: C22.1, U1.36, Y1.1
XIN32: C24.1, U1.48, Y2.P$2
XOUT: C21.1, U1.35, Y1.3
XOUT32: C23.1, U1.49, Y2.P$1
XT1: C39.1, IC6.1, R9.1, Y4.1
XT2: C40.1, IC6.2, R9.2, Y4.3
XUSB: C26.1, F1.2, U1.39, USB1.1
XVCC: F2.2, J3.P1

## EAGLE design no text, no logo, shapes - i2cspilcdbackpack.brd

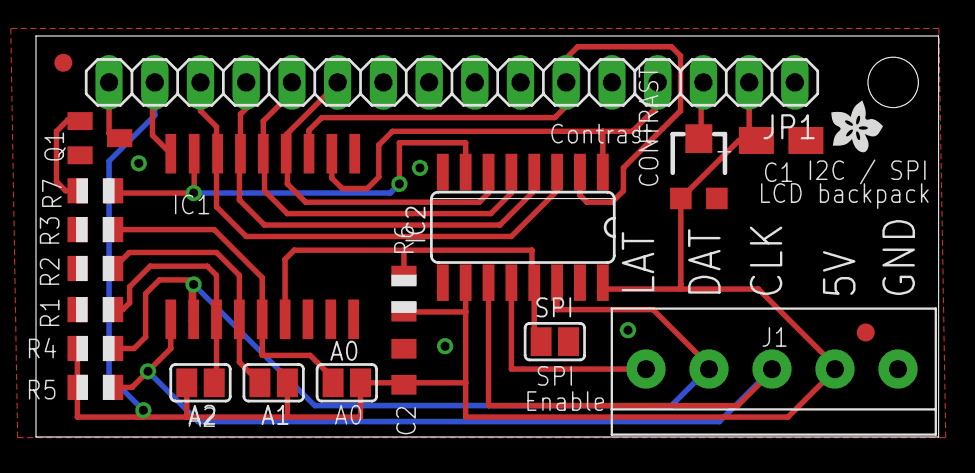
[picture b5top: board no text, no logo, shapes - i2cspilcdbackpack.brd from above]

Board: 2 copper layers, 50.1 x 22.3 mm, 22 parts (0 on the bottom side), 19 nets.

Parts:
A0, A1, A2: SJ
C1: 10uF; A/3216-18R
C2: 0.1uF; C0805K
CONTRAST: 10K; TC33X
IC1: MCP2300X/SO; SO18W
IC2: 74LS595D; SO16
J1: 1X5; 3.5MM-5P
JP1: 1X16
Q1: SOT23-BEC
R1, R2, R3, R6, R7: 10k; R0805
R4, R5: 4.7k; R0805
SPI: SJ
U$1, U$2: FIDUCIAL; FIDUCIAL_1MM
U$3: ADAFRUIT200MIL

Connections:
CLOCK: IC1.1, IC2.11, J1.3, R5.1
DATA: IC1.2, IC2.14, J1.4, R4.1
DB4: IC1.13, IC2.6, JP1.11
DB5: IC1.14, IC2.5, JP1.12
DB6: IC1.15, IC2.4, JP1.13
DB7: IC1.16, IC2.3, JP1.14
E: IC1.12, IC2.2, JP1.6
GND: C1.-, C2.2, CONTRAST.3, IC1.9, IC2.8, J1.1, JP1.1, JP1.5, Q1.E, R1.1, R2.1, R3.1, SPI.1
LATCH: IC2.12, J1.5
LITE: IC1.17, IC2.7, R7.1
unnamed: A0.2, IC1.5, R3.2
unnamed: A1.2, IC1.4, R2.2
unnamed: A2.2, IC1.3, R1.2
unnamed: IC1.6, IC2.13, R6.2, SPI.2
unnamed: JP1.16, Q1.C
unnamed: Q1.B, R7.2
unnamed: CONTRAST.2, JP1.3
RS: IC1.11, IC2.1, JP1.4
VCC: A0.1, A1.1, A2.1, C1.+, C2.1, CONTRAST.1, IC1.18, IC2.10, IC2.16, J1.2, JP1.2, JP1.15, R4.2, R5.2, R6.1

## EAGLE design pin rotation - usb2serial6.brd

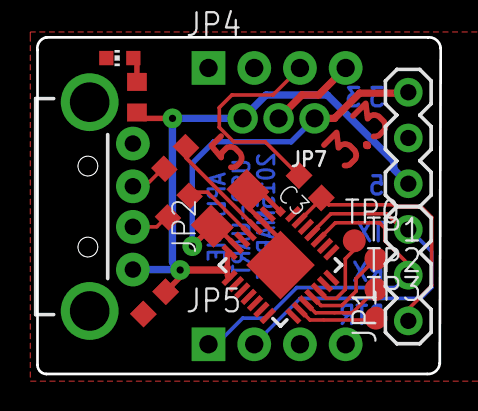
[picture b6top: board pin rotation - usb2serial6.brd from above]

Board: 2 copper layers, 22.4 x 18.7 mm, 18 parts (0 on the bottom side), 17 nets.

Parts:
C1: 10uF; C1206
C2: 1uF; C0603K
C3: C0603K
IC1: CP2103_USB_UART; MLP28
JP1, JP3: 1X03
JP2: USB-A-H
JP4, JP5: 1X04_NO_SILK
JP7: 1X03_2MM
LED1: CHIP-LED0603
R1, R2: 22; R0603
R4: 470; R0603
TP0, TP1, TP2, TP3: TPB1,27; B1,27

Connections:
DTR: C3.1, IC1.27, JP1.1
GND: C2.2, IC1.7, IC1.8, JP2.VBUS, JP3.3, JP7.3, R4.1
IO0: IC1.19, TP0.TP
IO1: IC1.18, TP1.TP
IO2: IC1.17, TP2.TP
IO3: IC1.16, TP3.TP
unnamed: IC1.3, R1.2
unnamed: IC1.4, R2.2
unnamed: LED1.A, R4.2
unnamed: C1.1, C2.1, IC1.2, IC1.EXP, IC1.M, JP2.GND, JP3.2, JP4.2, JP5.4, LED1.C
RST: C3.2, JP4.3
RXD: IC1.24, JP1.2, JP5.1
TXD: IC1.25, JP1.3, JP5.2
USBD+: JP2.D+, R1.1
USBD-: JP2.D-, R2.1
VCC: JP4.4, JP7.2
VCC3.3: C1.2, IC1.6, JP3.1, JP7.1

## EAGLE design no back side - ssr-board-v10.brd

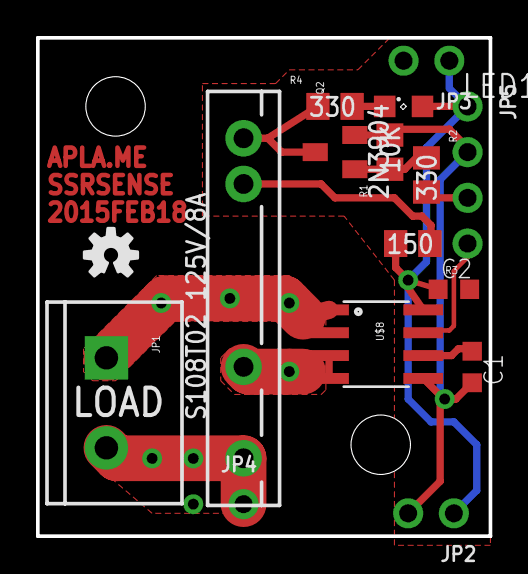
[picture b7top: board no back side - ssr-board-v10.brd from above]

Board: 2 copper layers, 25.1 x 27.7 mm, 19 parts (0 on the bottom side), 12 nets.

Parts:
C1, C2: C0603K
JP1: Load; SCREWTERMINAL-5MM-2
JP2, JP3: 1X02_ROUND
JP4: 1X01_ROUND
JP5: 1X04_ROUND
LED1: SML0805
Q2: 2N3904; SOT23
R1: 10K; R0805
R2, R4: 330; R0805
R3: 150; R0805
U1: S108T02; RELAY-S108T02
U$2: OSHW-LOGO; OSHW-LOGO-S
U$4, U$7: STAND-OFF
U$8: ACS712; SO08
U$9: CREATIVE_COMMONS

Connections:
5V: C2.1, JP2.1, JP3.1, JP5.1, LED1.A, R3.2, U$8.8
COIL: Q2.3, R4.1, U1.4
CTL: JP5.3, R2.2
CURRENT: JP5.4, U$8.7
FILTER: C1.1, U$8.6
GND: C1.2, C2.2, JP2.2, JP3.2, JP5.2, Q2.2, R1.2, U$8.5
LOAD1: JP1.2, JP4.1, U1.1
LOAD2: U1.2, U$8.3, U$8.4
LOADSENSE: JP1.1, U$8.1, U$8.2
unnamed: R3.1, U1.3
unnamed: Q2.1, R1.1, R2.1
unnamed: LED1.C, R4.2

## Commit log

2017-11-29 initial set of boards to test with viewee.js

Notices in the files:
RAMPS_1-3i.brd:
GPL3
GPL v3
Copyright 2011 Johnny Russell - UltiMachine
parts and their libraries:
SparkFun: Released under the Creative Commons Attribution Share-Alike 3.0 License
SparkFun: http://creativecommons.org/licenses/by-sa/3.0
SparkFun-AnalogIC: Licensing:Creative Commons ShareAlike 4.0 International - https://creativecommons.org/licenses/by-sa/4.0
